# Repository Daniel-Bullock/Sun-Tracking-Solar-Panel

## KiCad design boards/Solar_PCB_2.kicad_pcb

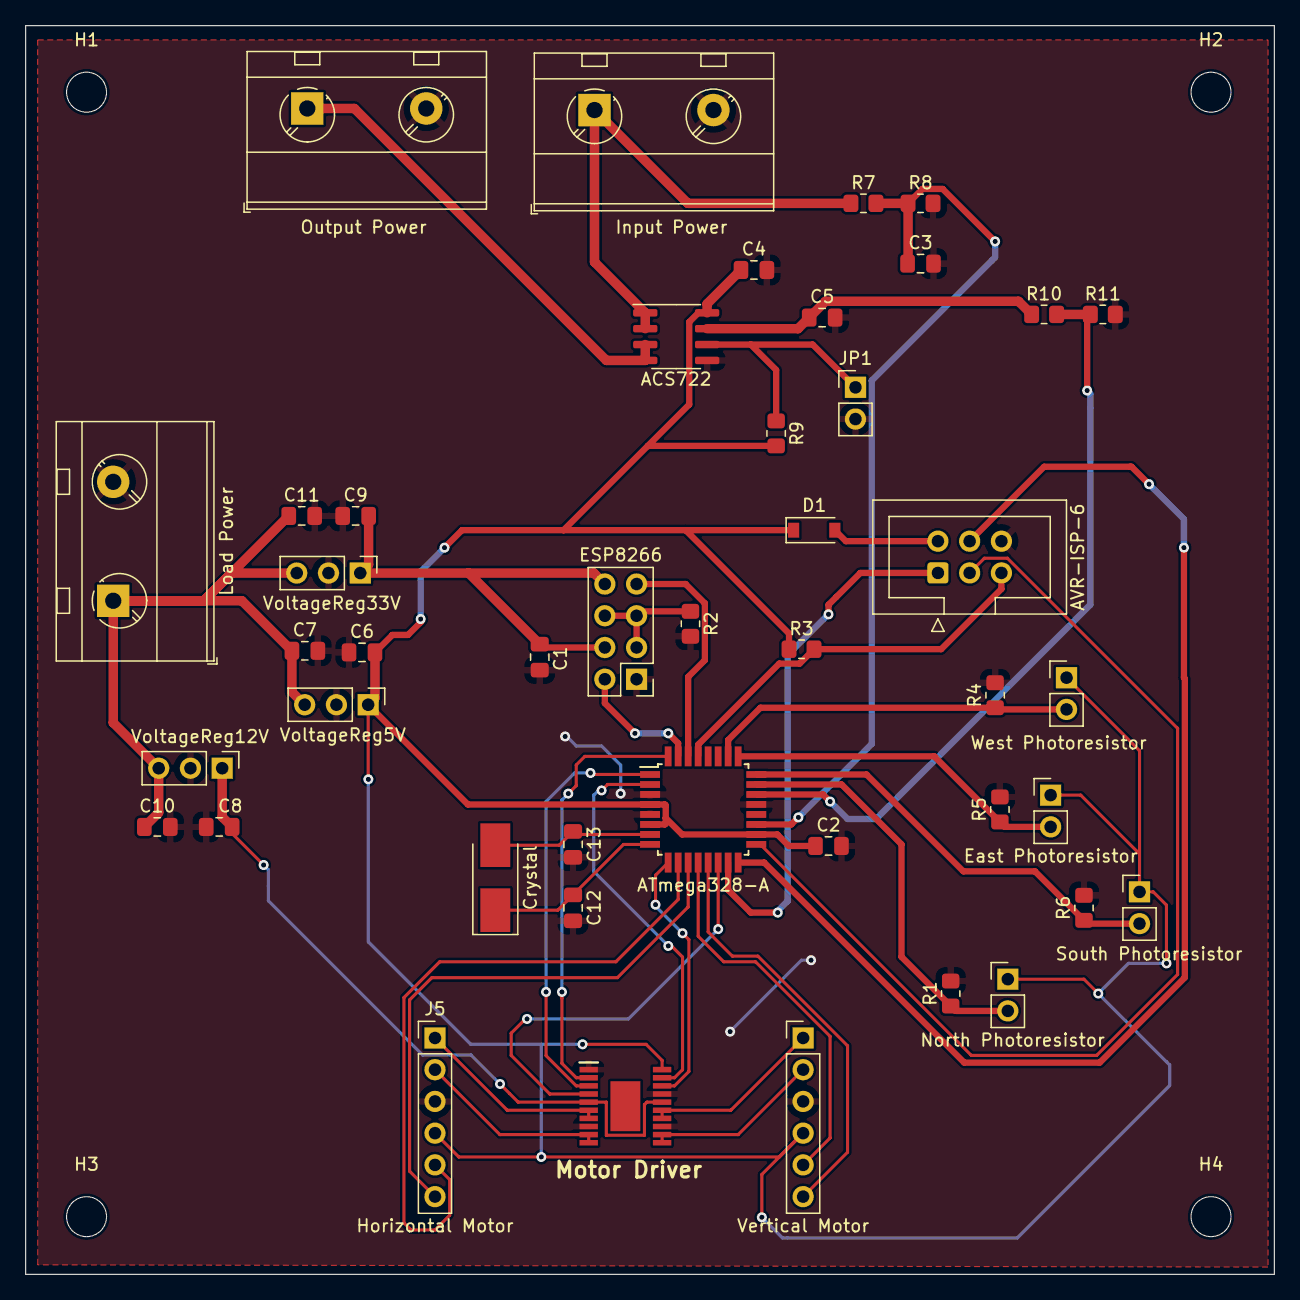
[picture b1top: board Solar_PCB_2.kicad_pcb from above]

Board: 2 copper layers, 99.9 x 99.9 mm, 48 parts (0 on the bottom side), 38 nets.

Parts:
C1, C2, C6, C7, C8, C9, C10, C11: 1uF; C_0805_2012Metric_Pad1.18x1.45mm_HandSolder
C3, C4: .1uF; C_0805_2012Metric_Pad1.18x1.45mm_HandSolder
C5: 1nF; C_0805_2012Metric_Pad1.18x1.45mm_HandSolder
C12, C13: 22p; C_0805_2012Metric_Pad1.18x1.45mm_HandSolder
D1: MBR0520; D_SOD-123
H1, H2, H3, H4: MountingHole; MountingHole_3.2mm_M3
J1: Motor Driver; BD635
J1#2: ESP8266; PinHeader_2x04_P2.54mm_Vertical
J2: AVR-ISP-6; IDC-Header_2x03_P2.54mm_Vertical
J3: North Photoresistor; PinHeader_1x02_P2.54mm_Vertical
J4: West Photoresistor; PinHeader_1x02_P2.54mm_Vertical
J5: Horizontal Motor; PinHeader_1x06_P2.54mm_Vertical
J6: East Photoresistor; PinHeader_1x02_P2.54mm_Vertical
J7: South Photoresistor; PinHeader_1x02_P2.54mm_Vertical
J8: Vertical Motor; PinHeader_1x06_P2.54mm_Vertical
J9: Input Power; TerminalBlock_MetzConnect_Type703_RT10N02HGLU_1x02_P9.52mm_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
J10: Output Power; TerminalBlock_MetzConnect_Type703_RT10N02HGLU_1x02_P9.52mm_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
J11: VoltageReg5V; PinHeader_1x03_P2.54mm_Vertical
J12: Load Power; TerminalBlock_MetzConnect_Type703_RT10N02HGLU_1x02_P9.52mm_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
J13: VoltageReg12V; PinHeader_1x03_P2.54mm_Vertical
J14: VoltageReg33V; PinHeader_1x03_P2.54mm_Vertical
JP1: Jumper_2_Bridged; PinHeader_1x02_P2.54mm_Vertical
R1, R2, R3, R4, R5, R6, R7: 10k; R_0805_2012Metric_Pad1.20x1.40mm_HandSolder
R8: 3.8k; R_0805_2012Metric_Pad1.20x1.40mm_HandSolder
R9: 4.7k; R_0805_2012Metric_Pad1.20x1.40mm_HandSolder
R10: 1k; R_0805_2012Metric_Pad1.20x1.40mm_HandSolder
R11: 2k; R_0805_2012Metric_Pad1.20x1.40mm_HandSolder
U1: ACS722; SOIC-8_3.9x4.9mm_P1.27mm
U2: ATmega328-A; TQFP-32_7x7mm_P0.8mm
Y1: Crystal; Crystal_SMD_5032-2Pin_5.0x3.2mm_HandSoldering

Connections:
+3V3: C1.1, C9.2, J1#2.4, J1#2.8, J14.1
+5V: C2.1, C4.1, C6.2, D1.1 (K), J1.20 (VCC), J3.1, J4.1, J5.4, J6.1, J7.1, J8.4, J11.1, R3.1, R9.2, U1.8 (VCC), U2.4 (VCC), U2.6 (VCC), U2.18 (AVCC)
+12V: C8.2, J1.5 (VM_1), J1.16 (VM_2), J13.1
/B+: C7.1, C10.1, C11.1, J11.3, J12.1, J13.3, J14.3
/EAST: J6.2, R5.1, U2.25 (PC2)
/H_ENC_A: J5.5, U2.10 (PD6)
/H_ENC_B: J5.6, U2.11 (PD7)
/IN1A: J1.2 (IN1A), U2.32 (PD2)
/IN1B: J1.3 (IN1B), U2.1 (PD3)
/IN2A: J1.19 (IN2A), U2.2 (PD4)
/IN2B: J1.18 (IN2B), U2.9 (PD5)
/MISO: J2.1 (MISO), U2.15 (PB3)
/MOSI: J2.4 (MOSI), U2.16 (PB4)
/MP_H+: J1.6 (OUT1A_1), J1.7 (OUT1A_2), J5.1
/MP_H-: J1.9 (OUT1B_1), J1.10 (OUT1B_2), J5.2
/MP_V+: J1.14 (OUT2A_1), J1.15 (OUT2A_2), J8.1
/MP_V-: J1.11 (OUT2B_1), J1.12 (OUT2B_2), J8.2
/NORTH: J3.2, R1.1, U2.23 (PC0)
/PANEL_CURRENT: R10.2, R11.1, U2.22 (ADC7)
/PANEL_DIVIDER: J9.1, R7.1, U1.1 (IP+), U1.2 (IP+)
/PANEL_VOLTAGE: C3.1, R7.2, R8.1, U2.19 (ADC6)
/PWM: J1.4 (PWM), U2.14 (PB2)
/RESET: J2.5 (~RST), R3.2, U2.29 (~RESET/PC6)
/RXI: J1#2.7, U2.30 (PD0)
/SCK: J2.3 (SCK), U2.17 (PB5)
/SOUTH: J7.2, R6.1, U2.24 (PC1)
/TXO: J1#2.2, U2.31 (PD1)
/VIOUT: C5.1, R10.1, U1.7 (VIOUT)
/V_ENC_A: J8.5, U2.12 (PB0)
/V_ENC_B: J8.6, U2.13 (PB1)
/WEST: J4.2, R4.1, U2.26 (PC3)
GND: C1.2, C2.2, C3.2, C4.2, C5.2, C6.1, C7.2, C8.1, C9.1, C10.2, C11.2, C12.2, C13.2, J1.1 (GND), J1.8 (PGND_1), J1.13 (PGND_2), J1.17 (PS), J1#2.1, J2.6 (GND), J5.3, J8.3, J9.2, J10.2, J11.2, J12.2, J13.2, J14.2, JP1.2 (B), R1.2, R2.2, R4.2, R5.2, R6.2, R8.2, R11.2, U1.5 (GND), U2.3 (GND), U2.5 (GND), U2.21 (GND)
unnamed: C12.1, U2.8 (XTAL2/PB7), Y1.1
unnamed: C13.1, U2.7 (XTAL1/PB6), Y1.2
unnamed: D1.2 (A), J2.2 (VCC)
unnamed: J1#2.3, J1#2.5, J1#2.6, R2.1
unnamed: J10.1, U1.3 (IP-), U1.4 (IP-)
unnamed: JP1.1 (A), R9.1, U1.6 (BW_SEL)

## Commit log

2022-02-07 Add new directory
2022-02-07 structure
2022-02-08 2/7/2022_lab_notebook_entry.md
2022-02-08 Add new file
2022-02-11 Update 2_10
2022-05-06 files upload
